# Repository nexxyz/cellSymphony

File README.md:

# Cell Symphony

Cell Symphony is a desktop-first hardware-instrument prototype that turns cellular automata into music. The Tauri desktop app is a 1:1 simulator for the planned hardware control surface, not a separate product UX.

> **Work in progress.** This is an active hobby project. Interfaces and behavior can change quickly, but the README should reflect the current implemented state.

---

## What It Is

Cell Symphony combines a pluggable cellular-behavior engine, a hardware-parity menu/control layer, and a realtime synth/sample backend:

- An **8x8 grid** runs one of 10 pluggable algorithms via the shared `BehaviorEngine` API.
- A **sense/mapping layer** turns cell transitions (`activate`, `stable`, `deactivate`, `scanned`) into musical events.
- A **voice layer** manages instruments, synth/sample/MIDI slots, mixer routing, FX buses, and sample-grid assignments.
- A **Touch performance layer** provides grid pages for mix, pan, and mapped momentary FX.
- A **desktop simulator** mirrors the hardware interface, including OLED, grid LEDs, encoders, buttons, transport, MIDI, and audio bridge behavior.

---

## Current Status

Implemented and functional:

- 10 behaviors: none, sequencer, keys, Conway Life, Brian's Brain, Langton's Ant, Bounce, Shapes, Raindrops, DLA, and Glider.
- Multi-part L1/L2 architecture with per-part behavior, scan/sense settings, mapping, names, and saved grid state.
- Scanning modes, sectioned scanning, scan direction, state/event triggers, and pitch/velocity/filter modulation lanes.
- Internal synth, sample slots, MIDI output/input, external sync, voice stealing policy, and audio load indicators.
- L3 Voice instruments with synth/sample/MIDI types, mixer volume/pan/route, FX buses, and sample assignment mode.
- L4 Touch performance layer with Mix, Pan, and FX pages.
- Touch FX mapping: select effect type/params, Map to Grid, press cells for momentary activate/release effects.
- Preset/default storage, factory/default load/save, auto-save, contextual help, OLED rendering, toast feedback, and aux encoder bindings.
- CI-style TypeScript/Rust lint, typecheck, test, and build scripts.

Planned/follow-up:

- Global/master FX workflow refinements.
- Aux mapping enhancements for the Touch context.
- Hardware prototype on Raspberry Pi Zero 2 W with NeoTrellis/NeoKeys/OLED/audio DAC.

---

## Controls

| Hardware Control | Simulator Key | Function |
|---|---|---|
| Main encoder turn | Left / Right | Move cursor or adjust edited value |
| Main encoder press | Enter | Enter group, toggle/edit value, confirm action |
| Back | Backspace / Esc | Back/exit edit/exit assignment mode |
| Space | Space | Play / pause |
| Shift + Space | Shift + Space | Emergency stop / panic |
| Shift + Back | Shift + Backspace / Shift + Esc | Clear active part grid |
| Fn + left grid column | Ctrl/Fn + left column | Select active part |
| Fn + right grid column | Ctrl/Fn + right column | Toggle Touch layer on/off |
| Touch right grid column | right column, no Fn | Select Touch page: mix, pan, fx |
| Aux encoder press | simulator aux control | Bind/unbind current menu item |
| Aux encoder turn | simulator aux control | Adjust bound parameter |

When Fn is held, the left grid column shows part options and the right grid column shows Touch page options. The active part/page is highlighted.

---

## Menu Overview

The authoritative menu/control spec lives in `docs/menu-and-controls-spec.md`.

- **L1: Life** — per-part behavior, step rate, behavior config, saved grid state, part naming.
- **L2: Sense** — per-part scan mode, scan axis/unit/direction/sections, trigger routing, note mapping, modulation lanes.
- **L3: Voice** — instruments, synth/sample/MIDI settings, sample assignment, mixer volume/pan/route, FX buses.
- **L4: Touch** — Touch Page, BPM, Touch FX type/params, Map to Grid.
- **Playback** — BPM.
- **System** — presets/defaults/factory, sound settings, MIDI, UI settings, contextual help.

---

## Touch Layer

`Fn + rightmost grid column` selects Touch pages. `Fn + leftmost grid column` selects a part to display and exits Touch.

- **mix**: columns are instruments, y=0 mutes and y=7 sets 100% volume.
- **pan**: rows are instruments, x=0 is hard left and x=7 is hard right.
- **fx**: assigned cells trigger momentary effects while held.

Touch FX maps cells to global-output momentary DSP in the Rust realtime engine:

- `stutter`
- `freeze`
- `filter_sweep`
- `pitch_shift`

To map FX, go to `L4: Touch > FX Page`, select an effect type and parameters, choose `Map to Grid`, then press a grid cell. The platform capability limit is 4 simultaneous held effects; same effect type presses replace the existing active cell.

---

## Algorithms

| Algorithm | Package | Description |
|---|---|---|
| none | `@cellsymphony/behaviors-none` | Empty/no-op behavior |
| sequencer | `@cellsymphony/behaviors-sequencer` | Manual grid toggle |
| keys | `@cellsymphony/behaviors-keys` | Momentary key grid |
| life | `@cellsymphony/behaviors-life` | Conway's Game of Life with optional spawning |
| brain | `@cellsymphony/behaviors-brain` | Brian's Brain 3-state automaton |
| ant | `@cellsymphony/behaviors-ant` | Langton's Ant |
| bounce | `@cellsymphony/behaviors-bounce` | Bouncing particles |
| shapes | `@cellsymphony/behaviors-pulse` | Expanding ring/shape pulses |
| raindrops | `@cellsymphony/behaviors-raindrops` | Falling drops and splash rings |
| dla | `@cellsymphony/behaviors-dla` | Diffusion-limited aggregation |
| glider | `@cellsymphony/behaviors-glider` | Conway glider spawning |

---

## Development

### Prerequisites

- Node.js 20+
- pnpm 9.12.0 (`corepack enable` recommended)
- Rust stable
- Tauri v2 prerequisites for desktop development

### Install

```bash
pnpm install
```

### Run Desktop Simulator

```bash
pnpm --filter @cellsymphony/desktop tauri:dev
```

On Windows you can also use:

```bash
cellSymphony.bat
```

### Verify

```bash
pnpm run build
pnpm run lint
pnpm run typecheck
pnpm run test
pnpm run test:coverage
cargo fmt --all --check
cargo clippy --workspace --exclude cellsymphony-pi --exclude cellsymphony-desktop --exclude midi-io-sidecar --exclude rodio-engine-source --all-targets -- -D warnings
cargo test --workspace --exclude cellsymphony-pi --exclude cellsymphony-desktop --exclude midi-io-sidecar --exclude rodio-engine-source
```

Run focused package tests with:

```bash
pnpm --filter @cellsymphony/platform-core test
pnpm --filter @cellsymphony/desktop test
```

The current platform-core suite has 144 tests after the Touch FX and section-order coverage additions.

---

## Project Structure

```text
cellSymphony/
├── apps/desktop/                  # Tauri desktop simulator and audio bridge
├── packages/
│   ├── platform-core/             # Core runtime, menu, transport, input routing, simulator frames
│   ├── behavior-api/              # BehaviorEngine interface and registry
│   ├── device-contracts/          # Shared device/display/grid contracts
│   ├── interpretation-core/       # Grid transitions and scan interpretation
│   ├── mapping-core/              # Musical intent to event mapping
│   ├── musical-events/            # Musical event contracts
│   ├── behaviors-*/               # Pluggable behavior packages
│   └── midi-headless-runner/      # Headless MIDI integration support
├── crates/
│   ├── realtime-engine/           # Rust realtime synth/sample/FX engine
│   ├── rodio-engine-source/       # Rodio source wrapper
│   ├── cellsymphony-hal/          # Hardware abstraction layer
│   └── cellsymphony-pi/           # Raspberry Pi app target
├── docs/                          # Specs, backlog, architecture, quality docs
├── hardware/                      # Hardware prototype resources
└── tools/                         # Auxiliary tools
```

---

## Documentation

- `docs/menu-and-controls-spec.md` — source of truth for menu/control behavior.
- `docs/backlog.md` — requirement status and phase planning.
- `docs/runtime-boundaries.md` — layer responsibilities.
- `docs/engineering-quality-requirements.md` — CI, coverage, and quality gates.
- `docs/implementation-done.md` — implementation summary for the initial 10-algorithm phase.

---

## Sample Library Attribution

The repository `samples/` content is sourced from the Stargate sample pack:

`https://github.com/stargatedaw/stargate-sample-pack`

---

## Hardware Plan

The long-term goal is a standalone hardware device:

- Raspberry Pi Zero 2 W
- 128x128 OLED display
- 5 clickable rotary encoders
- 4 NeoKey buttons
- 8x8 NeoTrellis grid
- PCM5102 I2S audio DAC
- USB-C power
- MIDI in/out where practical

---

## License

Copyright (c) 2026 nexxyz (Thomas Steirer).

**Free for personal/non-commercial use**: you may use, copy, modify, and build this software for personal purposes.

**Commercial use or selling hardware devices** requires prior written permission.

To request permission, contact: https://github.com/nexxyz

See the [LICENSE](LICENSE) file for full terms.

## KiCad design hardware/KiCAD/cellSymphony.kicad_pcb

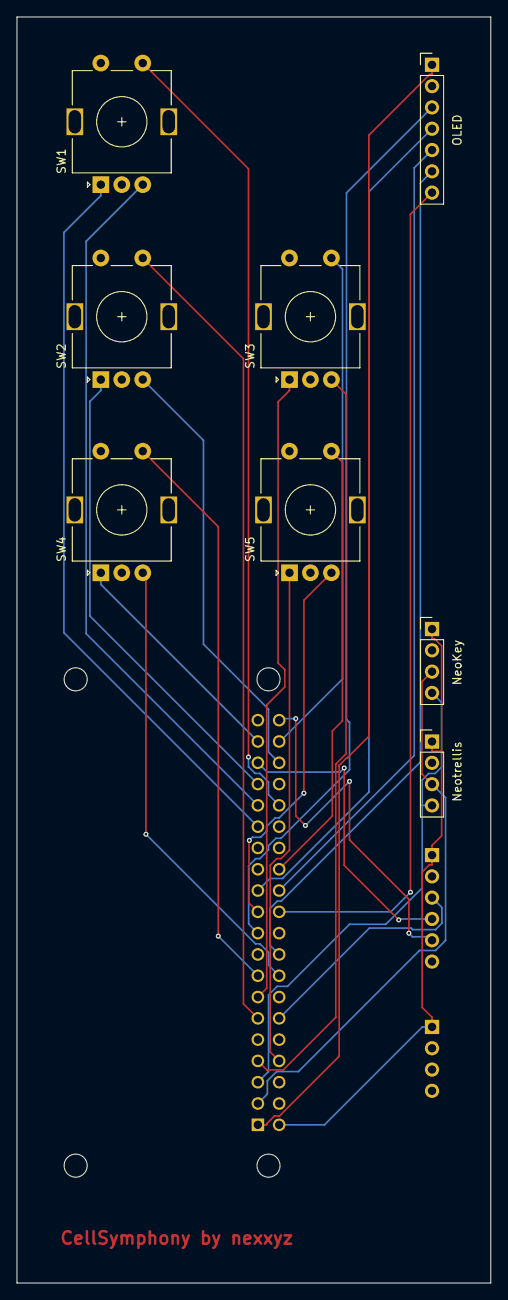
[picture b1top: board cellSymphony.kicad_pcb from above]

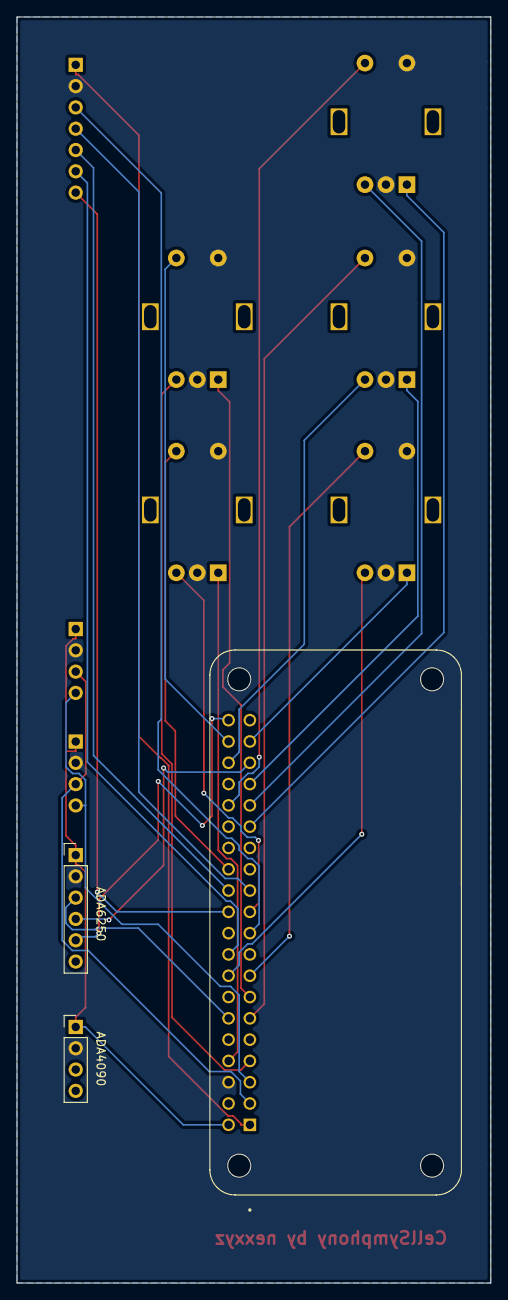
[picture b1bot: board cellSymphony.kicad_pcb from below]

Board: 2 copper layers, 56.5 x 151.0 mm, 11 parts (3 on the bottom side), 28 nets.

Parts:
ADA4090: Conn_01x04; PinHeader_1x04_P2.54mm_Vertical
ADA6250: Conn_01x06; PinHeader_1x06_P2.54mm_Vertical
NeoKey: Conn_01x04; PinHeader_1x04_P2.54mm_Vertical
Neotrellis: Conn_01x04; PinHeader_1x04_P2.54mm_Vertical
OLED: Conn_01x07; PinHeader_1x07_P2.54mm_Vertical
SW1, SW2, SW3, SW4, SW5: RotaryEncoder_Switch; RotaryEncoder_Alps_EC11E-Switch_Vertical_H20mm
U1: Raspberry Pi Zero 2 W; MODULE_RASPBERRY_PI_ZERO_2_W

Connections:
+5V: ADA4090.1 (VBUS), ADA6250.1 (VIN), NeoKey.1 (VIN), Neotrellis.1 (VIN), U1.2 (5V_2)
GND: ADA4090.2 (GND), ADA6250.2 (GND), NeoKey.2 (GND), Neotrellis.2 (GND), OLED.2 (GND), SW1.C, SW1.S2, SW2.C, SW2.S2, SW3.C, SW3.S2, SW4.C, SW4.S2, SW5.C, SW5.S2, U1.6 (GND_6)
unnamed: ADA6250.3 (BCK), U1.12 (GPIO18/GPIO_GEN1)
unnamed: ADA6250.5 (DIN), U1.40 (GPIO21)
unnamed: ADA6250.4 (LRCK), U1.35 (GPIO19)
unnamed: NeoKey.4 (SCL), Neotrellis.4 (SCL), U1.5 (GPIO3/SCL)
unnamed: NeoKey.3 (SDA), Neotrellis.3 (SDA), U1.3 (GPIO2/SDA1)
unnamed: OLED.4 (CLK), U1.23 (GPIO11/SPI_SCLK)
unnamed: OLED.5 (CS), U1.24 (GPIO8/SPI_~CE0)
unnamed: OLED.6 (DC), U1.18 (GPIO24/GPIO_GEN5)
unnamed: OLED.3 (MOSI), U1.19 (GPIO10/SPI_MOSI)
unnamed: OLED.7 (RST), U1.22 (GPIO25/GPIO_GEN6)
unnamed: OLED.1 (VIN), U1.1 (3V3_1)
unnamed: SW3.B, U1.7 (GPIO4/GPIO_GCLK)
unnamed: SW1.A, U1.29 (GPIO5)
unnamed: SW1.B, U1.31 (GPIO6)
unnamed: SW5.S1, U1.26 (GPIO7/SPI_~CE1)
unnamed: SW5.B, U1.21 (GPIO9/SPI_MISO)
unnamed: SW1.S1, U1.32 (GPIO12)
unnamed: SW2.A, U1.33 (GPIO13)
unnamed: SW5.A, U1.8 (GPIO14/TXD0)
unnamed: SW2.B, U1.36 (GPIO16)
unnamed: SW2.S1, U1.11 (GPIO17/GPIO_GEN0)
unnamed: SW3.S1, U1.38 (GPIO20)
unnamed: SW4.S1, U1.15 (GPIO22/GPIO_GEN3)
unnamed: SW4.B, U1.16 (GPIO23/GPIO_GEN4)
unnamed: SW4.A, U1.37 (GPIO26)
unnamed: SW3.A, U1.13 (GPIO27/GPIO_GEN2)

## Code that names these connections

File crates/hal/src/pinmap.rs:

//! Pin mapping for Cell Symphony hardware on Pi Zero 2W

/// I2C Bus 1 (GPIO2=SDA, GPIO3=SCL)
pub const I2C_BUS: u8 = 1;

/// SPI Bus 0
pub const SPI_BUS: &str = "/dev/spidev0.0";
pub const OLED_CS: u8 = 8; // GPIO8/CE0
pub const OLED_DC: u8 = 24; // GPIO24
pub const OLED_RST: u8 = 25; // GPIO25

/// I2S Pins
pub const I2S_BCK: u8 = 18; // GPIO18
pub const I2S_LRCK: u8 = 19; // GPIO19
pub const I2S_DIN: u8 = 21; // GPIO21

/// Encoder pins (A, B, Switch)
#[derive(Clone, Copy)]
pub struct EncoderPins {
    pub a: u8,
    pub b: u8,
    pub sw: u8,
}

/// 5 rotary encoders on Pi Zero 2W
pub const ENCODERS: [EncoderPins; 5] = [
    EncoderPins { a: 5, b: 6, sw: 12 }, // SW1 (main)
    EncoderPins {
        a: 13,
        b: 16,
        sw: 17,
    }, // SW2 (aux1)
    EncoderPins {
        a: 27,
        b: 4,
        sw: 20,
    }, // SW3 (aux2)
    EncoderPins {
        a: 26,
        b: 23,
        sw: 22,
    }, // SW4 (aux3)
    EncoderPins { a: 14, b: 9, sw: 7 }, // SW5 (aux4) - B=GPIO9 reused from SPI MISO
];

/// NeoKey I2C address (typically 0x30)
pub const NEOKEY_ADDR: u16 = 0x30;

/// NeoTrellis I2C addresses (4 devices, 4x4 each = 8x8 grid)
pub const TRELLIS_ADDRS: [u16; 4] = [0x2E, 0x2F, 0x30, 0x31];

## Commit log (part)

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2026-05-21 Split desktop Tauri support modules
2026-05-21 Move synth engine ownership to audio source
2026-05-21 Fix CI rust checks
2026-05-21 Update workflow actions for Node 24
2026-05-21 Pin pnpm in workflows
2026-05-21 Fix FX parameter defaults
2026-05-22 Add compressor + EQ FX bus effects, rename Bus to FX Bus
    Effects:
    - Compressor: envelope follower, threshold/ratio/attack/release/makeup/mix
    - EQ: 3-band with low shelf, peaking mid, high shelf via biquad filters
    Rename:
    - Canonical route IDs: bus_N -> fx_bus_N (old bus_N accepted on load)
    - UI labels: Bus N -> FX Bus N, Bus Slot -> FX Slot
2026-05-22 Lowercase all selectable pluggable names
    - Behavior display names: Sequencer→sequencer, Game of Life→game of life, etc.
    - Synth preset labels: Init→init, Soft Pad→soft pad, etc.
    - FX effect group labels: Duck→duck, Delay→delay, Compressor→compressor, EQ→eq, etc.
    - Updated tests, docs, and TSV help entries to match
2026-05-24 Auto-save cooldown, coalesced audio config, toast helper, aux stale binding, naming migration, geometric bars, numeric display mode, FX state preservation, and backlog document
    - Auto-save cooldown: deferred 2s trailing writes for config edits, immediate for explicit saves
    - Coalesced audio config sender: signature-gated setInstruments to avoid unnecessary IPC
    - Toast helper: centralized makeToast() with scrolling support on OLED
    - Aux stale binding: scoped 'not active' toasts on inactive aux use (no proactive unbinding)
    - Naming migration: autoName/name replaces nameMode/customName across instruments, buses, parts
    - Geometric bar rendering: smooth fillRect bars with numChars-based position
2026-05-26 Add Touch FX mapping and fix navigation
2026-05-26 Fix Touch grid navigation, mixer volume, FX cap, and autosave
2026-05-27 Add Phase 5: Rust Core Migration (REQ-19)
2026-05-27 Fix cargo fmt formatting in engine.rs and tests.rs
2026-05-27 Fix missing volume field in Pi app InstrumentMixerConfig init
2026-05-28 Touch: aux mapping overlay, FX targets, remove Playback
2026-05-28 Aux: reserve OLED line, expand auto-map
2026-05-29 Aux: mapping overlay paths and scroll
2026-05-29 Aux: persist manual bindings
2026-05-31 feat(platform-core): auto-save 'S' flash indicator; replace stateEnabled with inputEventsWhilePaused
    - Add autoSaveFlash/autoSaveFlashUntilMs to SystemState, initialized in initialState
    - Tick decay clears autoSaveFlash after 500ms via Date.now().equals(nowMs())
    - Render 'S' glyph at OLED top-right in splash and normal modes (oledRender)
    - Wire autoSaveFlash through simulatorFrameBuilder to desktop runtime
    - Add isAuto? flag to save_default_result StoreResult
    - applyStoreResult: isAuto=true => flash only, no toast; manual save => flash + toast
2026-05-31 fix: dedup behavior reinit in inputRouter, centralize aux encoder helpers, fix spread syntax
2026-05-31 fix(typecheck): resolve 3 TS errors from refactor
    - Add explicit type annotation to factoryPayload callbacks in index.ts
    - Move handleTouchGridPress to inputInternal.ts (conflict with local definition)
    - Fix TouchGridDeps to use 'any' types to avoid generic instantiation conflicts
2026-06-01 fix(platform-core): events bypass scan mode gate
    Events from grid transitions now fire independently of scan cursor state.
    Previous condition skipped entire interpretGrid() block when scanMode was
    'scanning' and scanAdvanced was false, dropping event triggers.
    Test updated to disable events so scan-advance behavior still isolates correctly.
2026-06-01 feat: replace shift double-tap with Fn+Shift for sample column assignment
    - Shift alone selects the whole row during sample assignment
    - Fn+Shift selects the whole column (was Shift double-tap)
    - Remove sampleAssignLastPress state and SAMPLE_ASSIGN_REPEAT_WINDOW_MS
    - Update docs, help text, and test to match
2026-06-01 Small bugfixes and improvements
2026-06-01 feat: Implement centralized Shift+Fn combined modifier handling
2026-06-01 feat: rename thirdModifierHeld to combinedModifierHeld for clarity
2026-06-02 Implement effective combined modifier handling
2026-06-02 Add Fn and combined modifier LED states
2026-06-02 Fn+Play toggles global trigger mute instead of partPaused
    - Added system.triggerMuted flag (SystemState, default false)
    - Fn+Play now toggles triggerMuted with 'Triggers on/off' toast
    - Implemented filterTriggerGatedIntents in both inputInternal.ts and
    runtimeHelpers.ts — returns [] when muted (active part only),
    otherwise filters by per-cell triggerGates
    - Added filterTriggerGatedIntents gate in inputRouter.ts input
2026-06-03 Panning improvements, UI cleanup, device/simulator parity
2026-06-03 Wire shift+aux press to assignAuxEncoder; add pnpm test to pre-push hook
    - Add shift+aux encoder press handler in inputRouter.ts that calls
    assignAuxEncoder for binding/unbinding current menu parameter
    - Fix 4 pre-existing test failures in features-aux.test.ts that
    relied on this missing wiring
    - Add pnpm test step to .githooks/pre-push (all 180 tests pass)
2026-06-03 feat: filter and flatten L4: Dance menu by active touchMode
    Make L4: Dance children a function that shows only page-relevant items:
    Dance Page and BPM always first, then FX Page or Trigger Gate (flat: true)
    when the corresponding touchMode is active. Hide irrelevant page groups
    when on mix/pan/none pages. Cursor re-maps to edited enum after tree
    reorder. Rename 'Edit Target' to 'Target Part' in Trigger Gate.
2026-06-03 fix selected label alignment shifting left 1 char when highlighted
    menuPresentation.ts: add 1 space to selected label and value prefixes
    so that selected text aligns with unselected text. Value remains
    +1 indent from label.
2026-06-04 clean up repo: remove debug scripts, KiCAD backups, merge scripts/ into tools/
    - Delete 11 root-level debug/test scripts (dev artifacts)
    - git rm 8 KiCAD backup zips, add backups/ to .gitignore
    - Move pi-zero image zip from root to tools/pi-image/
    - Merge scripts/quality-audit.mjs into tools/, delete scripts/
2026-06-04 README refresh: fix stale counts, add trigger-gate docs, separate dev section
2026-06-04 docs: update README planned section - mark phase 1-3 and phase 4 completed items as implemented
2026-06-04 README: move CI note from Current Status into Dev > Verify
2026-06-04 docs: add REQ-05 and REQ-15 to planned section
2026-06-04 untrack .qwen/ and QWEN.md (AI tool config, not project source)
2026-06-04 docs: update backlog status - phase 1-3 complete, phase 4 partially complete
2026-06-05 githooks: move account checks to local hooks
2026-06-05 audio: add global fx master chain
2026-06-05 platform-core: persist dance mode state
2026-06-05 platform-core: fix dance help TSV rows
2026-06-07 platform-core: add probabilistic trigger gate
2026-06-07 platform-core: split sense menu builders
2026-06-07 platform-core: enforce specific menu help coverage
2026-06-07 platform-core: land source changes required by menu-help tests and fix pre-push hook
    - commit inputConfirm.ts, menuInput.ts, menuPresentation.ts changes
    that the earlier menu-help test commit depended on
    - fix brittle scroll=3 assertion to use >0 (OS-independent)
    - pre-push hook now runs checks against the committed tree
    (auto-stashes dirty worktree) for CI parity
2026-06-08 desktop: avoid NSIS bundling in CI smoke build
2026-06-14 runtime: add native playback parity
2026-06-14 runtime: close native parity gaps
2026-06-15 runtime: enforce native menu parity
2026-06-15 runtime: clarify host boundary names
2026-06-15 runtime: remove legacy ts engine
2026-06-15 runtime: centralize capabilities and refresh docs
2026-06-15 refactor: address architecture audit findings
2026-06-15 refactor: split native menu model
2026-06-15 refactor: split native runner helpers
2026-06-15 refactor: split native runner store handling
2026-06-15 refactor: split native runner config shaping
2026-06-15 refactor: split native runner snapshot rendering
2026-06-15 refactor: split native runner payload apply
2026-06-15 refactor: split native runner controls
2026-06-16 test: split native menu coverage
2026-06-16 test: split native runner coverage
2026-06-16 test: split desktop host adapter coverage
2026-06-18 hardware: add new PCB revision with KiCAD libs and reports
2026-06-20 perf: harden playback responsiveness
2026-06-20 hardware: add enclosure assets
2026-06-20 feat: add shutdown splash and 3-aux capability
2026-06-20 ci: install alsa dev package for Rust jobs
2026-06-20 refactor: split playback runtime modules
2026-06-20 ci: add per-crate Rust coverage gates
2026-06-20 desktop: fix simulator control layout
2026-06-20 test: split oversized runtime modules
2026-06-20 runtime: restore native ui pulse support
2026-06-20 test: remove local config assumptions
2026-06-21 desktop: finish native runtime parity
2026-06-21 docs: refresh hardware and architecture docs
2026-06-21 quality: split runtime and ui hotspots
2026-06-21 style: format refactored runtime modules
2026-06-21 style: format final runtime quality pass
2026-06-21 quality: split synth render voice path
2026-06-22 style: format remaining hotspot cleanup
2026-06-22 ux: improve hardware interface feedback
2026-06-22 style: keep sense menu under line limit
2026-06-22 docs: codify qa and file length rules
2026-06-22 docs: keep subagent policy out of AGENTS
2026-06-22 docs: codify portable exe rebuilds
2026-06-22 feat: prepare Pi appliance deployment
2026-06-22 feat: add Pi diagnostics and update hooks
2026-06-22 test: split trigger gate transport tests
2026-06-23 feat: add capability driven DSP budgets
2026-06-23 feat: balance synth voice stealing
2026-06-23 feat: update hardware I2C addresses
2026-06-23 chore: tune Pi appliance services
2026-06-23 fix: satisfy sample favourites clippy
2026-06-23 fix: satisfy pre-push quality checks
2026-06-23 test: remove low-value round trips
2026-06-24 perf: optimize native audio runtime
2026-06-24 fix: install Pi cross Rust target
2026-06-24 perf: skip inactive FX routing work
2026-06-24 perf: optimize native snapshot materialization
2026-06-24 perf: flatten runtime LED snapshots
2026-06-25 fix: improve menu display and autosave responsiveness
2026-06-25 perf: profile Pi render responsiveness
2026-06-25 chore: refresh default runtime preset
2026-06-26 fix: refresh menu after behavior auto-name changes
2026-06-26 perf: avoid Pi snapshot clone on render
2026-06-26 perf: speed current menu key resolution
2026-06-26 perf: combine menu snapshot row counts
2026-06-26 fix: persist portable default autosaves
2026-06-26 fix: reconcile auto-named part behavior changes
2026-06-26 fix: prefer edited menu row values
2026-06-27 fix: sanitize saved default payload
2026-06-27 test: cover persistent behavior serialization
2026-06-27 docs: clarify shippable work loops
2026-06-27 refactor: decouple runtime control paths
2026-06-27 fix: satisfy structural commit clippy
2026-06-27 docs: prioritize hardware user documentation
2026-06-28 fix: keep looper mode changes live-safe
2026-06-28 ci: add explicit release artifact pipeline
2026-06-28 ci: fix pi image stage file paths
2026-06-28 ci: export custom pi image stage
2026-06-29 polish menu controls and help
2026-06-29 polish modulation target selection
2026-06-30 refactor playback menu tests and formatting
2026-06-30 refactor runner and engine modules
2026-06-30 fix rodio telemetry default derive
2026-06-30 refactor remaining files under line target
2026-06-30 document responsibility review guidance
